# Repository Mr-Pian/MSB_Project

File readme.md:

# 2025 盟升杯电子设计竞赛 - G题：具有自动瞄准跟踪功能的激光通信系统

## 📖 项目简介 (Introduction)

本项目为 **2025 盟升杯电子设计竞赛** **[G题]** 的参赛工程源码及硬件方案，同时该设计采用了创新的**共轴光路**设计方案，从而达到更高精度的瞄准。
我们设计了一套**激光自动瞄准与跟踪通信系统**，系统分为发射端（TX）和接收端（RX），能够实现快速的目标搜索、锁定以及稳定的激光数据传输。

### 🎥 视频演示
我在 Bilibili 上录制了关于共轴光路的详细介绍和演示视频，欢迎观看！

👉 **[点击观看 B站视频演示](https://www.bilibili.com/video/BV11VFkzCEsm/?vd_source=f163b375ae59addf986a6a39b1f11695)**

---

## 📂 仓库目录结构 (Repository Structure)

本仓库包含了从硬件设计、嵌入式软件到机械结构的全部资料：

```text
MSB_Project/
├── 3D/                     # 机械结构文件
│   └── 云台3D.step         # 二维云台的3D建模文件
├── Document/               # 比赛相关文档
│   ├── G题...pdf           # 官方赛题说明
│   ├── SCH_...pdf          # 硬件weAct扩展板原理图 PDF 导出
│   └── MSB_parameters.txt  # 系统
├── firmware/               # 嵌入式控制源码
│   ├── MSB/                # [发射端主控] 基于 STM32H750VBT6（WeAct核心板）
│   │   ├── Control/        # 闭环控制算法 (PID, 云台控制)
│   │   ├── YunTai/         # 云台电机驱动逻辑
│   │   └── ...
│   ├── MSB_RX/             # [接收机主控] 基于 STM32F103C8T6
│   │   ├── Core/Src/oled.c # OLED 显示驱动
│   │   └── ...
│   └── laserrx/            # [激光接收器主控] 基于 STM32G031
├── hardware/               # 硬件工程文件
│   └── ms/                 # KiCad PCB 工程 (原理图与PCB源文件)
├── software/               # 上位机与仿真脚本
│   ├── smp/                # 树莓派视觉python脚本
│   └── naickp/             # 串口屏/UI 相关工程文件
└── README.md
```
## 🛠️ 硬件方案 (Hardware)

系统采用多MCU协同工作的架构：

| 模块 | 核心芯片 | 主要功能 |
| :--- | :--- | :--- |
| **发射端主控** | **STM32H750VBT6** | 负责云台姿态控制 (PID)、激光调制 |
| **视觉识别** | **Rpi5** | 负责图像识别 |
| **接收器主控** | **STM32G031** | 负责解调信号、显示通信数据 |
| **接收机旋转调速主控** | **STM32F103C8T6** | 负责接收机转速设置 |
| **PCB设计** | **KiCad** | 开源EDA工具设计的双层/四层板 |
| **显示交互** | ST7735 / OLED | 实时显示系统状态与接收文字 |

## 💻 软件与算法 (Software & Algorithms)

### 1. 嵌入式控制 (Firmware)
- **控制算法**：在 `firmware/MSB/Control` 中实现了增量式 **PID算法**，用于二维云台的高精度闭环控制。
- **驱动开发**：包含步进电机/舵机驱动 (`DMR4315`)、激光调制驱动等。
- **开发环境**：STM32CubeMX + Keil / CMake。

### 2. 视觉识别 (CV)
- 在 `software/smp` 目录下提供了在树莓派5上运行的 **Python** 脚本。
- 实现了 **卡尔曼滤波 (Kalman Filter)** 的规矩验证 (`kalman_filter_module.py`)，用于预测目标轨迹，提高动态跟踪的鲁棒性。

## 🚀 使用说明 (Usage)

1.  **硬件制作**：
    - 参考 `hardware/ms` 下的 Gerber 文件或 KiCad 工程进行 PCB 打样与焊接。
    - 参考 `3D/` 目录打印机械结构件并组装。
2.  **固件烧录**：
    - 使用 ST-Link/Dap-Link 分别下载 `firmware` 目录下对应的 H750、F103 和 G031 固件。
3.  **系统联调**：
    - 上电后，发射端将自动运行自检并进入任务模式

## 🤝 贡献 (Contributing)

本项目由以下团队成员共同完成：

- **@Mr-Pian** - 队长 / 电控 / 机械
- **@PickaxeHit** - 接收器全栈 / 模拟部分设计
- **@nailong-xpy** - 视觉算法 / 接收机软件 / 串口屏

  <table>
  <tr>
    <td align="center">
      <a href="https://github.com/Mr-Pian">
        
        <br />
        <sub><b>Mr-Pian</b></sub>
      </a>
    </td>
    <td align="center">
      <a href="https://github.com/PickaxeHit">
        
        <br />
        <sub><b>PickaxeHit</b></sub>
      </a>
    </td>
    <td align="center">
      <a href="https://github.com/nailong-xpy">
        
        <br />
        <sub><b>nailong-xpy</b></sub>
      </a>
    </td>
  </tr>
</table>

如果你对本项目感兴趣，欢迎 Fork 和 Star！有问题请在 Issue 中提出。

---
*Created by Mr-Pian*

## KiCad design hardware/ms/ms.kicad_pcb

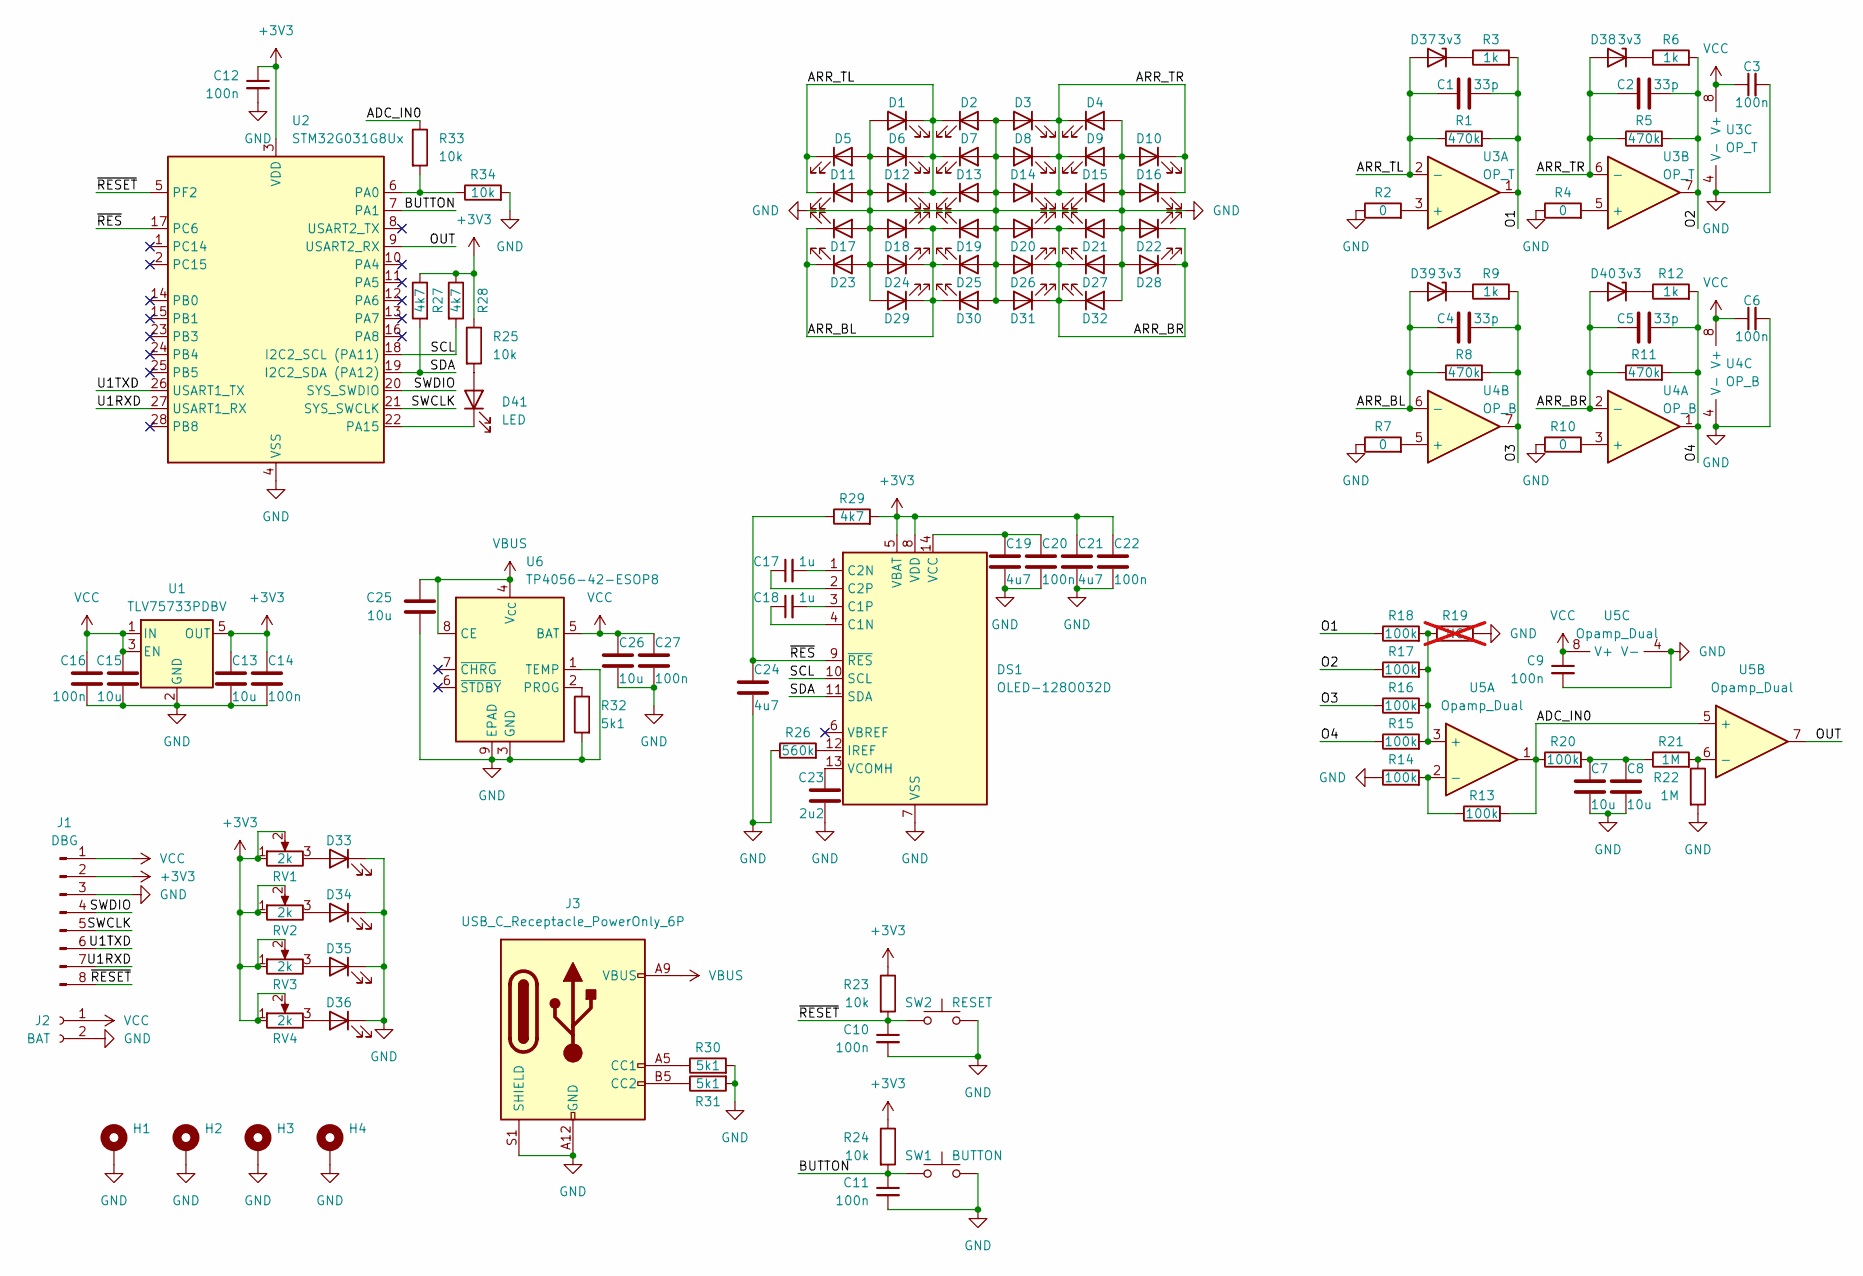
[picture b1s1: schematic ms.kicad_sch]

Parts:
C1, C2, C4, C5: 33p; C_0603_1608Metric
C3, C6, C9, C10, C11, C12, C14, C16, C20, C22, C27: 100n; C_0603_1608Metric
C7, C8, C13, C15, C25, C26: 10u; C_0603_1608Metric
C17, C18: 1u; C_0603_1608Metric
C19, C21, C24: 4u7; C_0603_1608Metric
C23: 2u2; C_0603_1608Metric
D1, D2, D3, D4, D5, D6, D7, D8, D9, D10, D11, D12, D13, D14, D15, D16, D17, D18, D19, D20, D21, D22, D23, D24, D25, D26, D27, D28, D29, D30, D31, D32, D33, D34, D35, D36: LED; LED_D5.0mm_Clear
D37, D38, D39, D40: 3v3; D_SOD-123
D41: LED; LED_0805_2012Metric
DS1: OLED-128O032D
H1, H2, H3, H4: MountingHole_Pad; MountingHole_3.2mm_M3_Pad
J1: DBG; PinHeader_1x08_P2.54mm_Vertical
J2: BAT; JST_XH_B2B-XH-A_1x02_P2.50mm_Vertical
J3: USB_C_Receptacle_PowerOnly_6P; USB_C_Receptacle_GCT_USB4125-xx-x_6P_TopMnt_Horizontal
R1, R5, R8, R11: 470k; R_0603_1608Metric
R2, R4, R7, R10: 0; R_0603_1608Metric
R3, R6, R9, R12: 1k; R_0603_1608Metric
R13, R14, R15, R16, R17, R18, R20: 100k; R_0603_1608Metric
R19: NC; R_0603_1608Metric; not fitted
R21, R22: 1M; R_0603_1608Metric
R23, R24, R25, R33, R34: 10k; R_0603_1608Metric
R26: 560k; R_0603_1608Metric
R27, R28, R29: 4k7; R_0603_1608Metric
R30, R31, R32: 5k1; R_0603_1608Metric
RV1, RV2, RV3, RV4: 2k; Potentiometer_Bourns_TC33X_Vertical
SW1: BUTTON; SW_Push_1P1T_NO_Vertical_Wuerth_434133025816
SW2: RESET; SW_Push_1P1T_NO_Vertical_Wuerth_434133025816
U1: TLV75733PDBV; SOT-23-5
U2: STM32G031G8Ux; QFN-28_4x4mm_P0.5mm
U3: OP_T; SOIC-8_3.9x4.9mm_P1.27mm
U4: OP_B; SOIC-8_3.9x4.9mm_P1.27mm
U5: Opamp_Dual; SOIC-8_3.9x4.9mm_P1.27mm
U6: TP4056-42-ESOP8; SOIC-8-1EP_3.9x4.9mm_P1.27mm_EP2.41x3.3mm

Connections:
+3V3: C12.1, C13.1, C14.1, C21.1, C22.1, DS1.5 (VBAT), DS1.8 (VDD), J1.2, R23.1, R24.1, R25.1, R27.1, R28.1, R29.2, RV1.1, RV1.2, RV2.1, RV2.2, RV3.1, RV3.2, RV4.1, RV4.2, U1.5 (OUT), U2.3 (VDD)
/ADC_IN0: R13.2, R20.1, R33.1, U5.1, U5.5 (+)
/ARR_BL: C4.1, D17.1 (K), D18.1 (K), D19.1 (K), D23.1 (K), D24.1 (K), D25.1 (K), D29.1 (K), D30.1 (K), D39.2 (A), R8.1, U4.6 (-)
/ARR_BR: C5.1, D20.1 (K), D21.1 (K), D22.1 (K), D26.1 (K), D27.1 (K), D28.1 (K), D31.1 (K), D32.1 (K), D40.2 (A), R11.1, U4.2 (-)
/ARR_TL: C1.1, D1.1 (K), D2.1 (K), D5.1 (K), D6.1 (K), D7.1 (K), D11.1 (K), D12.1 (K), D13.1 (K), D37.2 (A), R1.1, U3.2 (-)
/ARR_TR: C2.1, D3.1 (K), D4.1 (K), D8.1 (K), D9.1 (K), D10.1 (K), D14.1 (K), D15.1 (K), D16.1 (K), D38.2 (A), R5.1, U3.6 (-)
/BUTTON: C11.1, R24.2, SW1.1, U2.7 (PA1)
/O1: C1.2, R1.2, R3.2, R18.1, U3.1
/O2: C2.2, R5.2, R6.2, R17.1, U3.7
/O3: C4.2, R8.2, R9.2, R16.1, U4.7
/O4: C5.2, R11.2, R12.2, R15.1, U4.1
/OUT: U2.9 (USART2_RX), U5.7
/SCL: DS1.10 (SCL), R28.2, U2.18 (I2C2_SCL (PA11))
/SDA: DS1.11 (SDA), R27.2, U2.19 (I2C2_SDA (PA12))
/SWCLK: J1.5, U2.21 (SYS_SWCLK)
/SWDIO: J1.4, U2.20 (SYS_SWDIO)
/U1RXD: J1.7, U2.27 (USART1_RX)
/U1TXD: J1.6, U2.26 (USART1_TX)
/~RESET: C10.1, J1.8, R23.2, SW2.1, U2.5 (PF2)
/~RES: C24.1, DS1.9 (~RES), R29.1, U2.17 (PC6)
GND: C3.2, C6.2, C7.2, C8.2, C9.2, C10.2, C11.2, C12.2, C13.2, C14.2, C15.2, C16.2, C19.2, C20.2, C21.2, C22.2, C23.2, C24.2, C25.2, C26.2, C27.2, D1.2 (A), D2.2 (A), D3.2 (A), D4.2 (A), D5.2 (A), D6.2 (A), D7.2 (A), D8.2 (A), D9.2 (A), D10.2 (A), D11.2 (A), D12.2 (A), D13.2 (A), D14.2 (A), D15.2 (A), D16.2 (A), D17.2 (A), D18.2 (A), D19.2 (A), D20.2 (A), D21.2 (A), D22.2 (A), D23.2 (A), D24.2 (A), D25.2 (A), D26.2 (A), D27.2 (A), D28.2 (A), D29.2 (A), D30.2 (A), D31.2 (A), D32.2 (A), D33.1 (K), D34.1 (K), D35.1 (K), D36.1 (K), DS1.7 (VSS), H1.1, H2.1, H3.1, H4.1, J1.3, J2.2, J3.A12 (GND), J3.B12 (GND), J3.S1 (SHIELD), R2.1, R4.1, R7.1, R10.1, R14.1, R19.2, R22.2, R26.1, R30.2, R31.2, R32.2, R34.2, SW1.2, SW2.2, U1.2 (GND), U2.4 (VSS), U3.4 (V-), U4.4 (V-), U5.4 (V-), U6.1 (TEMP), U6.3 (GND), U6.9 (EPAD)
unnamed: C7.1, C8.1, R20.2, R21.1
unnamed: D33.2 (A), RV1.3
unnamed: D34.2 (A), RV2.3
unnamed: D35.2 (A), RV3.3
unnamed: D36.2 (A), RV4.3
unnamed: D37.1 (K), R3.1
unnamed: D38.1 (K), R6.1
unnamed: D39.1 (K), R9.1
unnamed: D40.1 (K), R12.1
unnamed: D41.2 (A), R25.2
unnamed: D41.1 (K), U2.22 (PA15)
unnamed: C18.1, DS1.4 (C1N)
unnamed: C18.2, DS1.3 (C1P)
unnamed: C17.2, DS1.1 (C2N)
unnamed: C17.1, DS1.2 (C2P)
unnamed: DS1.12 (IREF), R26.2
unnamed: C19.1, C20.1, DS1.14 (VCC)
unnamed: C23.1, DS1.13 (VCOMH)
unnamed: J3.A5 (CC1), R30.1
unnamed: J3.B5 (CC2), R31.1
unnamed: R33.2, R34.1, U2.6 (PA0)
unnamed: R2.2, U3.3 (+)
unnamed: R4.2, U3.5 (+)
unnamed: R10.2, U4.3 (+)
unnamed: R7.2, U4.5 (+)
unnamed: R15.2, R16.2, R17.2, R18.2, R19.1, U5.3 (+)
unnamed: R13.1, R14.2, U5.2 (-)
unnamed: R21.2, R22.1, U5.6 (-)
unnamed: R32.1, U6.2 (PROG)
VBUS: C25.1, J3.A9 (VBUS), J3.B9 (VBUS), U6.4 (V_{CC}), U6.8 (CE)
VCC: C3.1, C6.1, C9.1, C15.1, C16.1, C26.1, C27.1, J1.1, J2.1, U1.1 (IN), U1.3 (EN), U3.8 (V+), U4.8 (V+), U5.8 (V+), U6.5 (BAT)

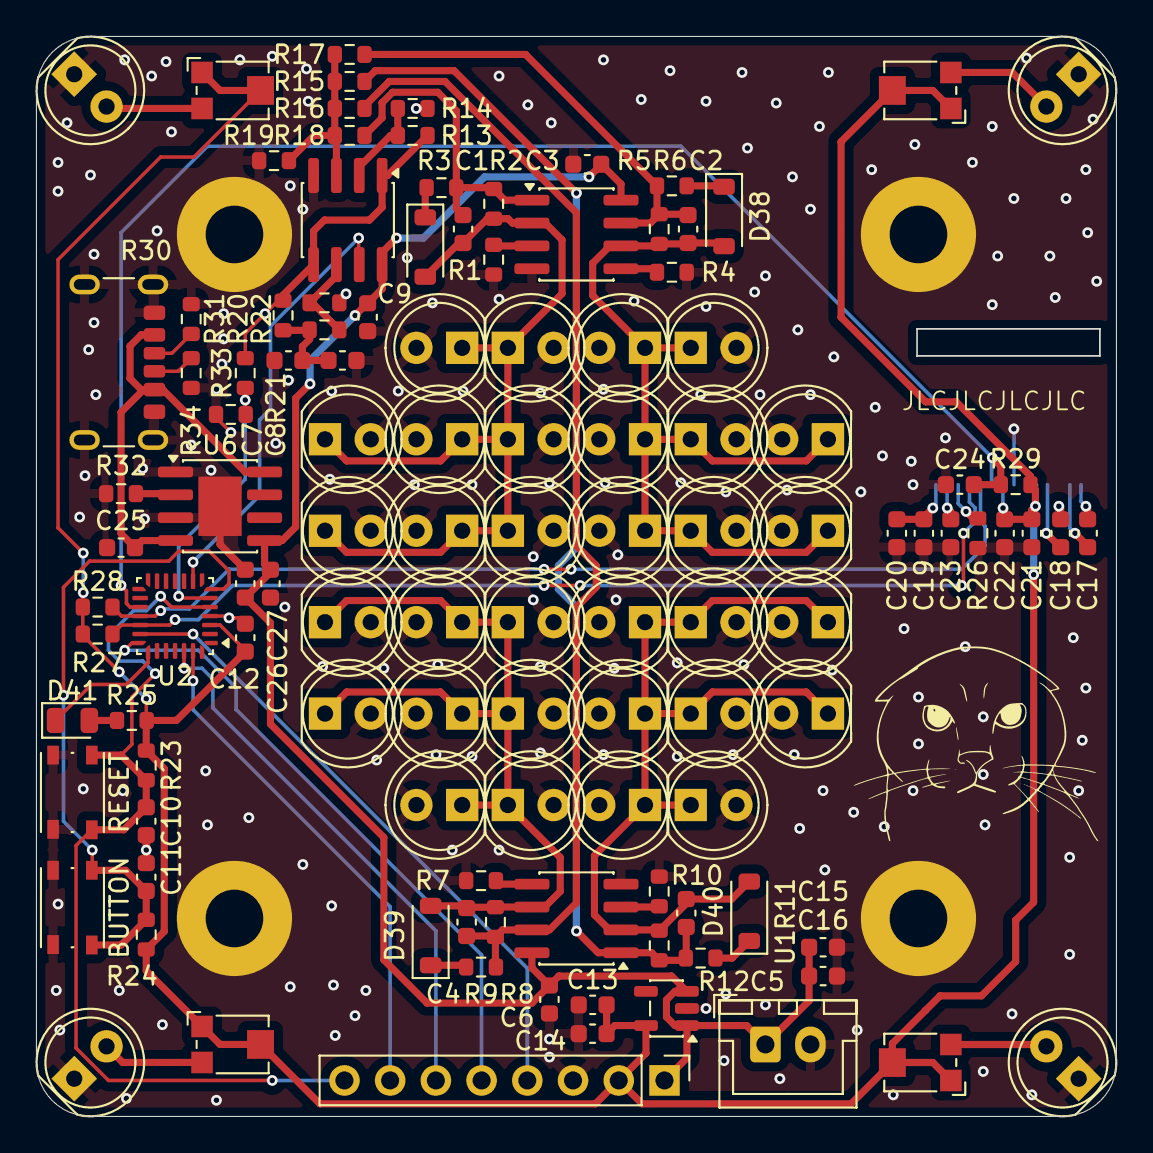
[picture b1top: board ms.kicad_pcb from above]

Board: 2 copper layers, 60.0 x 60.0 mm, 122 parts (1 on the bottom side), 52 nets.

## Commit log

2025-10-28 0.0.1
    最初版本
2025-10-28 0.0.2
    完善了下项目结构，控制架构并未写完
2025-10-29 增加了smp工程文件夹以及部分代码
2025-10-29 add readme
2025-10-29 init hardware
2025-10-29 0.1.0
    可以跟踪目标了，控制的大问题是5ms的控制周期太快导致两个电机不能都收到指令，现在是10ms然后电机自己的参数没有调整，导致移动很缓慢
2025-10-31 0.1.2
    对参数进行了调整，现在可以很快速的追踪光电，引入了HCI库，现在可以使用单按键简单控制模式
2025-11-01 0.1.3
    添加了题目
2025-11-03 0.1.4
    对set_zero_point 函数进行了修改，并修补了pid相对位置的小bug
2025-11-04 hardware update
2025-11-06 software添加了串口屏，视觉新增kalman滤波
2025-11-08 hw update for new design
2025-11-09 sch finished
2025-11-09 hw pcb init
2025-11-10 firmware SD卡完善
    1.更改了openocd 和 flash配置，完整的利用了h750 2m的flash
    2.挂载了Fatfs文件系统
    3.完成了从卡内读取参数，并保存的一系列接口
    4.HCI添加了闲置状态三击取消SD‘挂载（弹出卡）
2025-11-11 hw ver1
2025-11-11 hw rev2
2025-11-11 firmware与串口屏交互初步实现
    1.更换了LCD驱动库（爆改7735s方屏）
    2.使用串口空闲中断实现了和串口屏的通信
    3.设置瞄准点功能已经实现
2025-11-11 remove redundant font.h
2025-11-11 (almost)finished 1.1
2025-11-13 finished 1.2
2025-11-13 串口屏添加键盘
2025-11-13 增加XpyEncoder
2025-11-14 smp增加固定修正点，串口屏修bug
2025-11-14 在document里添加了主控板原理图
2025-11-16 firmware task1,2完善和修复bug
    1.修复了控制时基的bug,把电机控制频率提高到了100hz
    2.完善了task2的发送，task2已经初步完成
2025-11-17 基础问完成，等待串口屏写ui，等待徐培原写接收机
2025-11-17 add laser rx proj
2025-11-18 fw add MSB_RX
2025-11-18 fix bug
2025-11-18 fix more bugs
2025-11-18 fw MSB_RX rev
2025-11-19 fw add Sd parameters
2025-11-21 fw finished task 4/5
    扩展基本完成，等待写创新
2025-11-22 fw finished task 6
    创新点实现已完成，固件部分基本定型
2025-11-23 上传了报告参考
2025-11-24 update laser rx proj
2025-11-24 报告0.2
    1. 报告1.1基本完成，还差接收机的激光通信方案
    2. 方案描述绘制完成
    3. 后续章节部分改了名，当然章节结构可能还有点问题
2025-11-26 画了一些框图
2025-11-26 报告0.3
    1. 基本上3.2节之前的内容全部完成（差2.4接收机理论推导 差3.1.1 3.1.2接收机电路设计）
    2. 在hardware里添加了现在使用的主板的JLCeda文件
2025-11-26 hw add JLCproject
2025-11-26 update report
2025-11-26 ud rp
2025-11-27 报告0.4
2025-11-27 报告1.0
    除了结论，其他的基本整完了，需要弄一下格式
2025-11-28 报告最终版
2025-11-28 完赛
    完赛鲁鲁鲁
2026-01-10 noting
2026-02-07 final
    上传了3D模型，移除了报告
2026-02-07 Stop tracking 报告
2026-02-07 Revise README for 2025 competition project details
    Updated the README to provide project details for the 2025 盟升杯电子设计竞赛, including project introduction, repository structure, hardware solutions, software algorithms, and contribution information.

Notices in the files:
readme.md:
License: MIT
